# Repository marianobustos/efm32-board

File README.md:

# efm32-board
efm32 happy gecko board for lqfp48 parts

#### Schematic

[Schematic in pdf](efm32-board.pdf)

#### 3D view

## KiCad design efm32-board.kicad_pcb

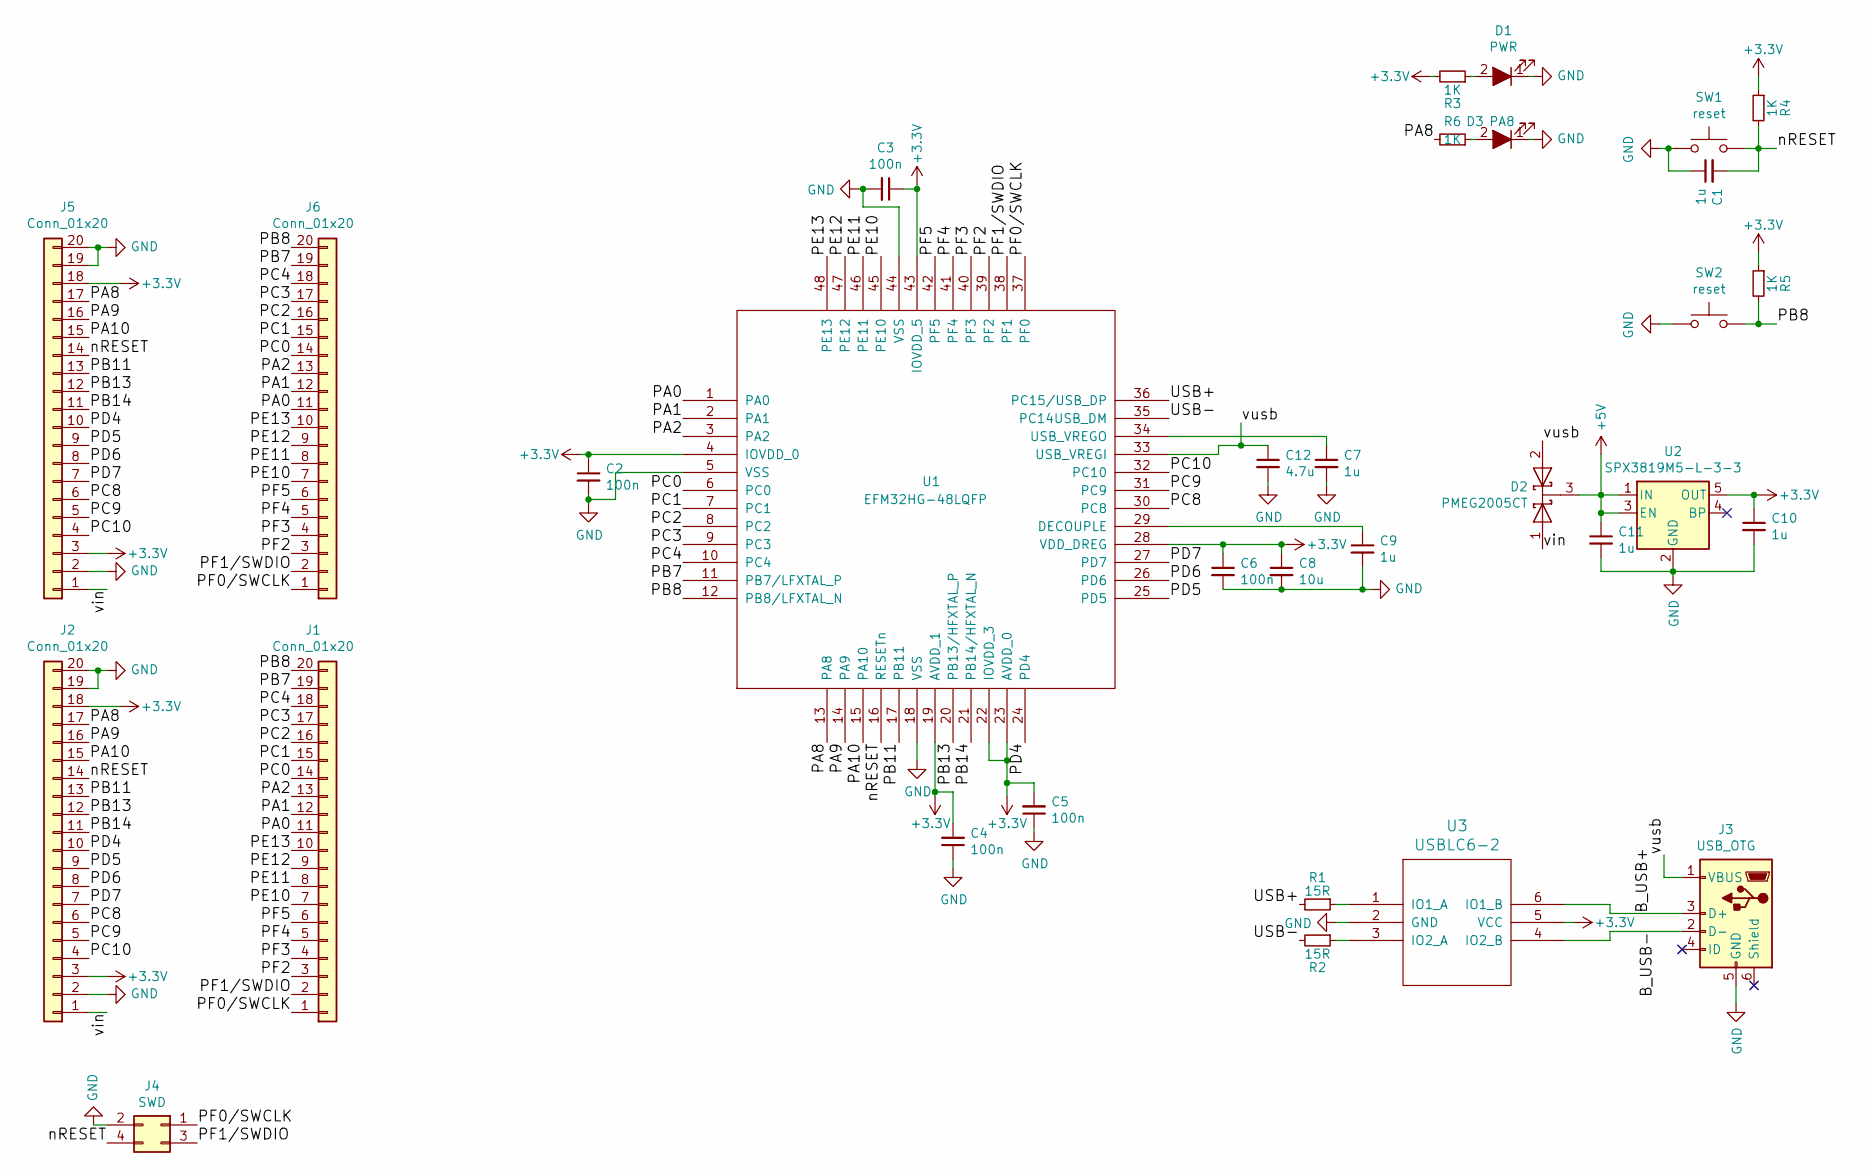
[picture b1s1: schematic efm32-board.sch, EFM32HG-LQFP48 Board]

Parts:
C1, C7, C9, C10, C11: 1u; C_0603
C2, C3, C4, C5, C6: 100n; C_0603
C8: 10u; C_0603
C12: 4.7u; C_0603
D1: PWR; LED_0805
D2: PMEG2005CT; SOT-23
D3: PA8; LED_0805
J1, J2, J5, J6: Conn_01x20; Pin_Header_Straight_1x20_Pitch2.54mm
J3: USB_OTG; USB_Micro-B_Molex_47346-0001
J4: SWD; Pin_Header_Straight_2x02_Pitch2.54mm_SMD
R1, R2: 15R; R_0603
R3, R4, R5, R6: 1K; R_0603
SW1, SW2: reset; SW_SPST_EVQPE1
U1: EFM32HG-48LQFP; LQFP-48_7x7mm_Pitch0.5mm
U2: SPX3819M5-L-3-3; SOT-23-5
U3: USBLC6-2; SOT-23-6

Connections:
+3V3: C2.1, C3.1, C4.2, C5.2, C6.1, C8.1, C10.1, J2.3, J2.18, J5.3, J5.18, R3.2, R4.1, R5.1, U1.4 (IOVDD_0), U1.19 (AVDD_1), U1.22 (IOVDD_3), U1.23 (AVDD_0), U1.28 (VDD_DREG), U1.43 (IOVDD_5), U2.5 (OUT), U3.5 (VCC)
+5V: C11.1, D2.3 (K), U2.1 (IN), U2.3 (EN)
/B_USB+: J3.3 (D+), U3.6 (IO1_B)
/B_USB-: J3.2 (D-), U3.4 (IO2_B)
/PA0: J1.11, J6.11, U1.1 (PA0)
/PA1: J1.12, J6.12, U1.2 (PA1)
/PA2: J1.13, J6.13, U1.3 (PA2)
/PA8: J2.17, J5.17, R6.2, U1.13 (PA8)
/PA9: J2.16, J5.16, U1.14 (PA9)
/PA10: J2.15, J5.15, U1.15 (PA10)
/PB7: J1.19, J6.19, U1.11 (PB7/LFXTAL_P)
/PB8: J1.20, J6.20, R5.2, SW2.2, U1.12 (PB8/LFXTAL_N)
/PB11: J2.13, J5.13, U1.17 (PB11)
/PB13: J2.12, J5.12, U1.20 (PB13/HFXTAL_P)
/PB14: J2.11, J5.11, U1.21 (PB14/HFXTAL_N)
/PC0: J1.14, J6.14, U1.6 (PC0)
/PC1: J1.15, J6.15, U1.7 (PC1)
/PC2: J1.16, J6.16, U1.8 (PC2)
/PC3: J1.17, J6.17, U1.9 (PC3)
/PC4: J1.18, J6.18, U1.10 (PC4)
/PC8: J2.6, J5.6, U1.30 (PC8)
/PC9: J2.5, J5.5, U1.31 (PC9)
/PC10: J2.4, J5.4, U1.32 (PC10)
/PD4: J2.10, J5.10, U1.24 (PD4)
/PD5: J2.9, J5.9, U1.25 (PD5)
/PD6: J2.8, J5.8, U1.26 (PD6)
/PD7: J2.7, J5.7, U1.27 (PD7)
/PE10: J1.7, J6.7, U1.45 (PE10)
/PE11: J1.8, J6.8, U1.46 (PE11)
/PE12: J1.9, J6.9, U1.47 (PE12)
/PE13: J1.10, J6.10, U1.48 (PE13)
/PF0/SWCLK: J1.1, J4.1, J6.1, U1.37 (PF0)
/PF1/SWDIO: J1.2, J4.3, J6.2, U1.38 (PF1)
/PF2: J1.3, J6.3, U1.39 (PF2)
/PF3: J1.4, J6.4, U1.40 (PF3)
/PF4: J1.5, J6.5, U1.41 (PF4)
/PF5: J1.6, J6.6, U1.42 (PF5)
/USB+: R1.2, U1.36 (PC15/USB_DP)
/USB-: R2.2, U1.35 (PC14USB_DM)
/nRESET: C1.2, J2.14, J4.4, J5.14, R4.2, SW1.2, U1.16 (RESETn)
/vin: D2.1 (A), J2.1, J5.1
/vusb: C12.1, D2.2 (A), J3.1 (VBUS), U1.33 (USB_VREGI)
GND: C1.1, C2.2, C3.2, C4.1, C5.1, C6.2, C7.2, C8.2, C9.2, C10.2, C11.2, C12.2, D1.1 (K), D3.1 (K), J2.2, J2.19, J2.20, J3.5 (GND), J4.2, J5.2, J5.19, J5.20, SW1.1, SW2.1, U1.5 (VSS), U1.18 (VSS), U1.44 (VSS), U2.2 (GND), U3.2 (GND)
unnamed: C7.1, U1.34 (USB_VREGO)
unnamed: C9.1, U1.29 (DECOUPLE)
unnamed: D1.2 (A), R3.1
unnamed: D3.2 (A), R6.1
unnamed: R1.1, U3.1 (IO1_A)
unnamed: R2.1, U3.3 (IO2_A)

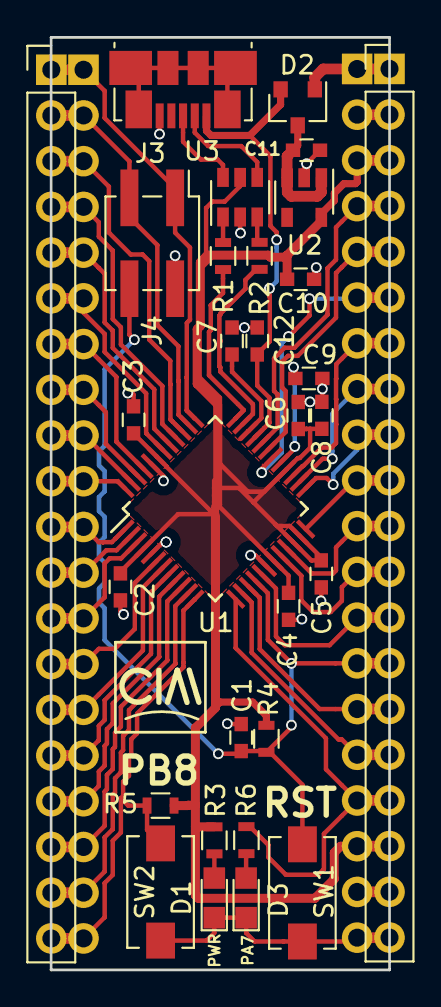
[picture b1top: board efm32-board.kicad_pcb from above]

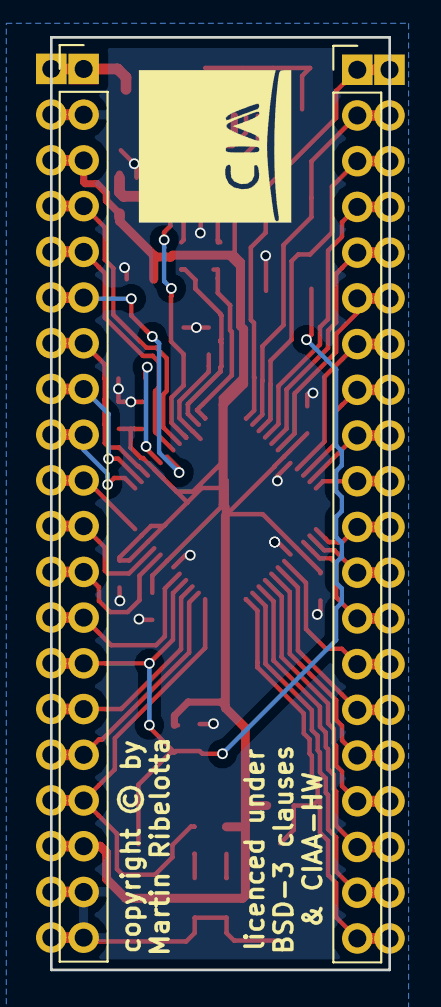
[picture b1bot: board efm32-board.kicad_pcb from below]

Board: 2 copper layers, 18.8 x 51.8 mm, 33 parts (3 on the bottom side), 49 nets.

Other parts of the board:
G102: LOGO_CIAA; LOGO-CIAA

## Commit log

2017-10-02 Rename <duino> to <board>
2017-10-02 Update readme link
2017-10-02 Cleanup
2017-10-03 Add +5v input diode array for split vbus and vin
2017-10-03 Update schematic and images
2017-10-03 Corrections and fixeds
2017-10-03 Add jump to pins 2-4 on J4 (SWD)
2017-10-03 Update schematic
2017-10-03 Change usb resistors from 22R to 15R
2017-10-03 Various fixes for release
2017-10-03 Update broken 3d view png
2017-10-03 Add +3v3 on pin 18 (previous GND) for prototyping convenience
2017-10-03 Add copyright and logo
2017-10-04 Add logos and copyright, export gerbers and bom
2017-10-04 Add dimention to PCB
2017-10-06 Modelo 3D pulsador y ocultar designators
    Se agregan los modelos 3D de los pulsadores y se ocultan los designator
    de J1/2/5/6 de la serigrafía porque estaban fuera de la placa.

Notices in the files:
efm32-board.kicad_pcb:
licenced under
BSD-3 clauses
copyright © by
Martin Ribelotta
